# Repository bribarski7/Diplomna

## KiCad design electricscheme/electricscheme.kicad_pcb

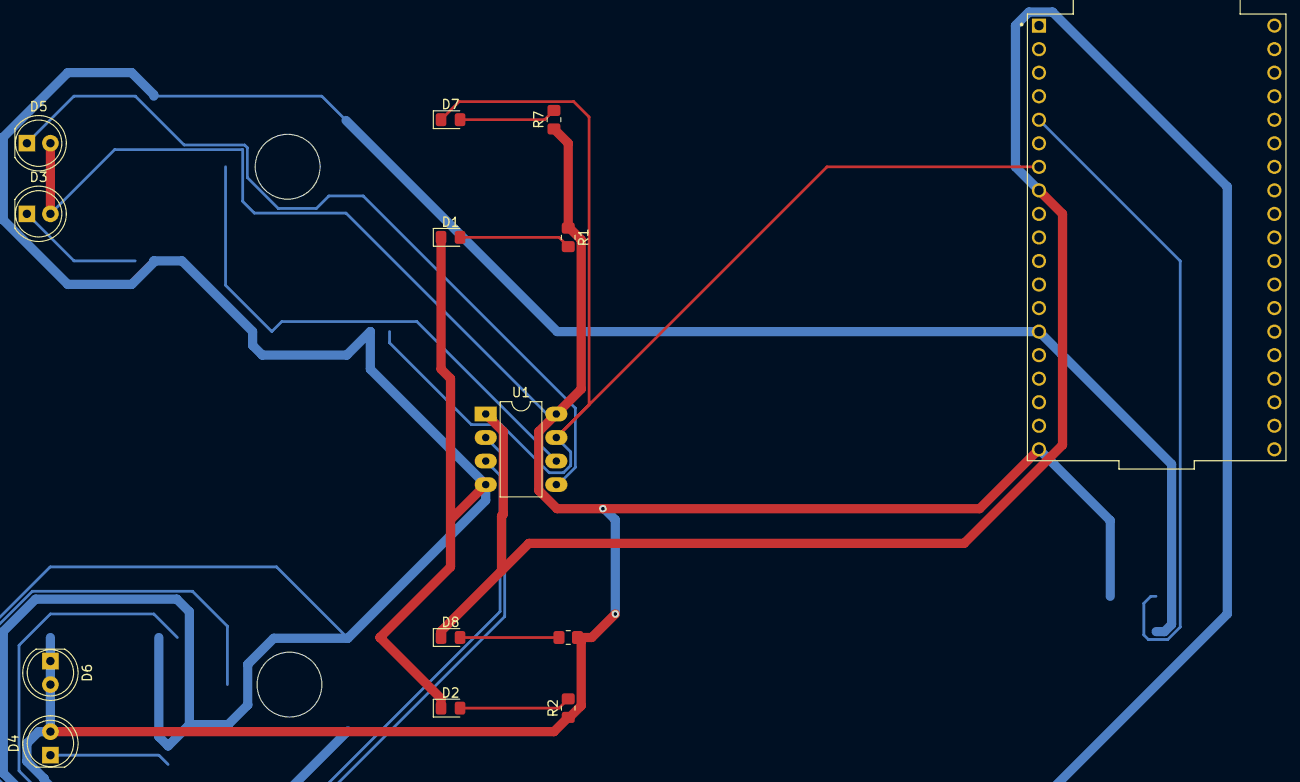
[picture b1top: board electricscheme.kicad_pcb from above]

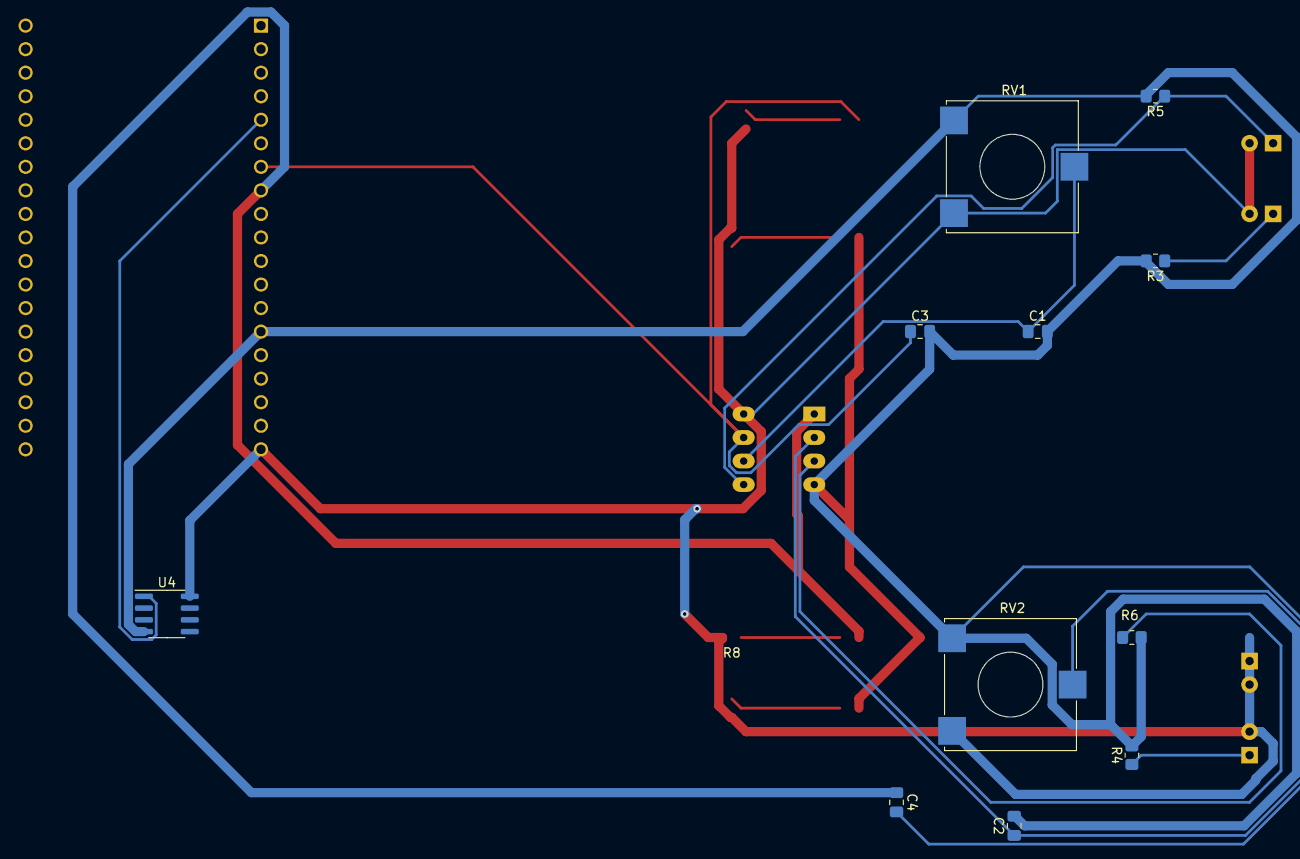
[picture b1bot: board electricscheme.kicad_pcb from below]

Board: 2 copper layers, 25 parts (11 on the bottom side), 15 nets.

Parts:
C1, C2, C3, C4: 0.1uF; C_0805_2012Metric_Pad1.18x1.45mm_HandSolder
D1, D2: POWER LED; LED_0805_2012Metric_Pad1.15x1.40mm_HandSolder
D3, D4: IR TX; LED_D5.0mm
D5, D6: IR RX; LED_D5.0mm
D7, D8: Detection LED; LED_0805_2012Metric_Pad1.15x1.40mm_HandSolder
R1, R2, R7, R8: 1k; R_0805_2012Metric_Pad1.20x1.40mm_HandSolder
R3, R4: 100; R_0805_2012Metric_Pad1.20x1.40mm_HandSolder
R5, R6: 10k; R_0805_2012Metric_Pad1.20x1.40mm_HandSolder
RV1, RV2: 10k; Potentiometer_ACP_CA14-VSMD_Vertical_Hole
U1: LM358; DIP-8_W7.62mm_LongPads
U3: ESP32-DEVKITC; MODULE_ESP32-DEVKITC
U4: LM35; SOIC-8_3.9x4.9mm_P1.27mm

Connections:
unnamed: C1.1, RV1.2, U1.6 (-)
unnamed: C1.2, C2.2, C3.2, C4.2, D1.1 (K), D2.1 (K), R3.2, R4.2, R5.2, R6.2, RV1.3, RV2.3, U1.4 (V-), U3.14 (GND1), U4.4 (GND)
unnamed: C2.1, RV2.2, U1.2 (-)
unnamed: C3.1, D7.1 (K), U1.7, U3.7 (IO32)
unnamed: C4.1, D8.1 (K), U1.1, U3.8 (IO33)
unnamed: D1.2 (A), R1.2
unnamed: D2.2 (A), R2.2
unnamed: D3.1 (K), R3.1
unnamed: D4.1 (K), R4.1
unnamed: D3.2 (A), D4.2 (A), D5.2 (A), D6.2 (A), R1.1, R2.1, R7.1, R8.1, RV1.1, RV2.1, U1.8 (V+), U3.19 (EXT_5V), U4.8 (+VS)
unnamed: D5.1 (K), R5.1, U1.5 (+)
unnamed: D6.1 (K), R6.1, U1.3 (+)
unnamed: D7.2 (A), R7.2
unnamed: D8.2 (A), R8.2
unnamed: U3.5 (IO34), U4.1 (Vout)

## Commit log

2022-02-22 GearLog class changes Top moving button
2022-02-22 Contact us edited home page
2022-02-23 Result page Added search by id functionality
2022-02-23 Removed unused files
2022-03-01 Error handling
2022-03-07 Fixing
2022-03-07 Edited log response
2022-03-16 Added part from hardware and fixing
